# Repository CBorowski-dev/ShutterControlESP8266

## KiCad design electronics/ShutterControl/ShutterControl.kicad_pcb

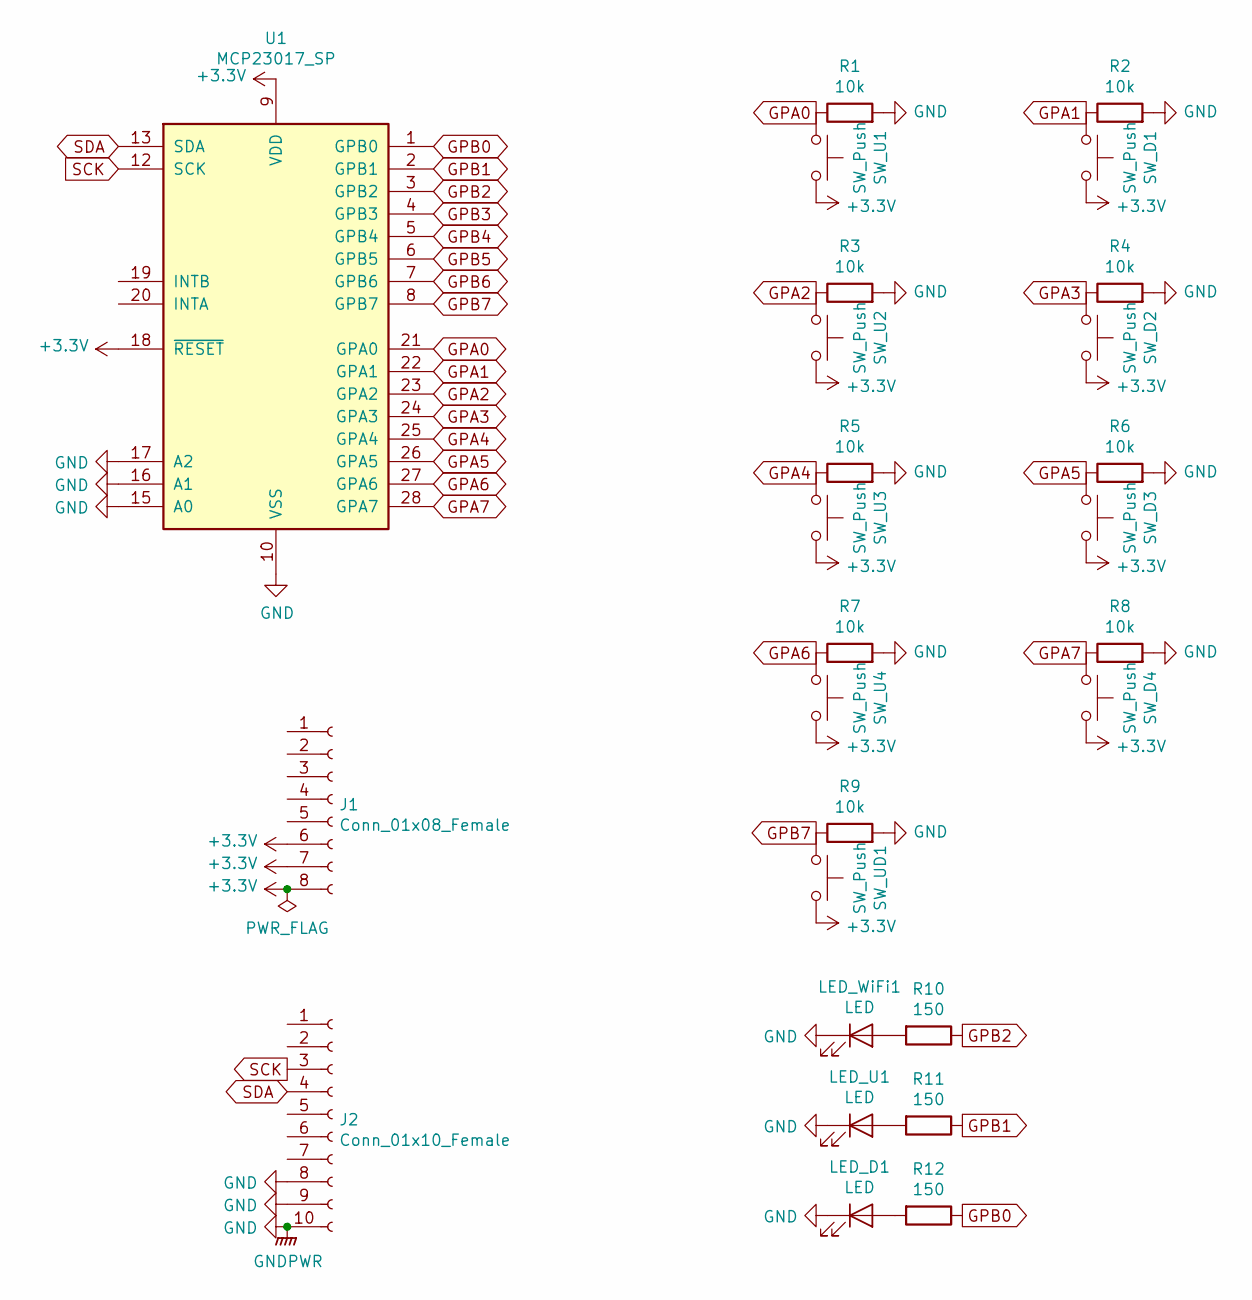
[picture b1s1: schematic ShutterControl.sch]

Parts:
J1: Conn_01x08_Female; PinHeader_1x08_P2.54mm_Vertical
J2: Conn_01x10_Female; PinHeader_1x10_P2.54mm_Vertical
LED_D1: LED; LED_D3.0mm_Clear
LED_U1: LED; LED_D3.0mm_Clear
LED_WiFi1: LED; LED_D3.0mm_Clear
R1, R2, R3, R4, R5, R6, R7, R8, R9: 10k; R_1206_3216Metric_Pad1.42x1.75mm_HandSolder
R10, R11, R12: 150; R_Axial_DIN0207_L6.3mm_D2.5mm_P2.54mm_Vertical
SW_D1, SW_D2, SW_D3, SW_D4: SW_Push; SW_PUSH_6mm_H7.3mm
SW_U1, SW_U2, SW_U3, SW_U4: SW_Push; SW_PUSH_6mm_H7.3mm
SW_UD1: SW_Push; SW_PUSH_6mm_H7.3mm
U1: MCP23017_SP; DIP-28_W7.62mm

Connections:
+3V3: J1.6, J1.7, J1.8, SW_D1.2, SW_D2.2, SW_D3.2, SW_D4.2, SW_U1.2, SW_U2.2, SW_U3.2, SW_U4.2, SW_UD1.2, U1.9 (VDD), U1.18 (~RESET~)
GND: J2.8, J2.9, J2.10, LED_D1.1 (K), LED_U1.1 (K), LED_WiFi1.1 (K), R1.2, R2.2, R3.2, R4.2, R5.2, R6.2, R7.2, R8.2, R9.2, U1.10 (VSS), U1.15 (A0), U1.16 (A1), U1.17 (A2)
GPA0: R1.1, SW_U1.1, U1.21 (GPA0)
GPA1: R2.1, SW_D1.1, U1.22 (GPA1)
GPA2: R3.1, SW_U2.1, U1.23 (GPA2)
GPA3: R4.1, SW_D2.1, U1.24 (GPA3)
GPA4: R5.1, SW_U3.1, U1.25 (GPA4)
GPA5: R6.1, SW_D3.1, U1.26 (GPA5)
GPA6: R7.1, SW_U4.1, U1.27 (GPA6)
GPA7: R8.1, SW_D4.1, U1.28 (GPA7)
GPB0: R12.1, U1.1 (GPB0)
GPB1: R11.1, U1.2 (GPB1)
GPB2: R10.1, U1.3 (GPB2)
GPB3: U1.4 (GPB3)
GPB4: U1.5 (GPB4)
GPB5: U1.6 (GPB5)
GPB6: U1.7 (GPB6)
GPB7: R9.1, SW_UD1.1, U1.8 (GPB7)
unnamed: LED_D1.2 (A), R12.2
unnamed: LED_U1.2 (A), R11.2
unnamed: LED_WiFi1.2 (A), R10.2
SCK: J2.3, U1.12 (SCK)
SDA: J2.4, U1.13 (SDA)

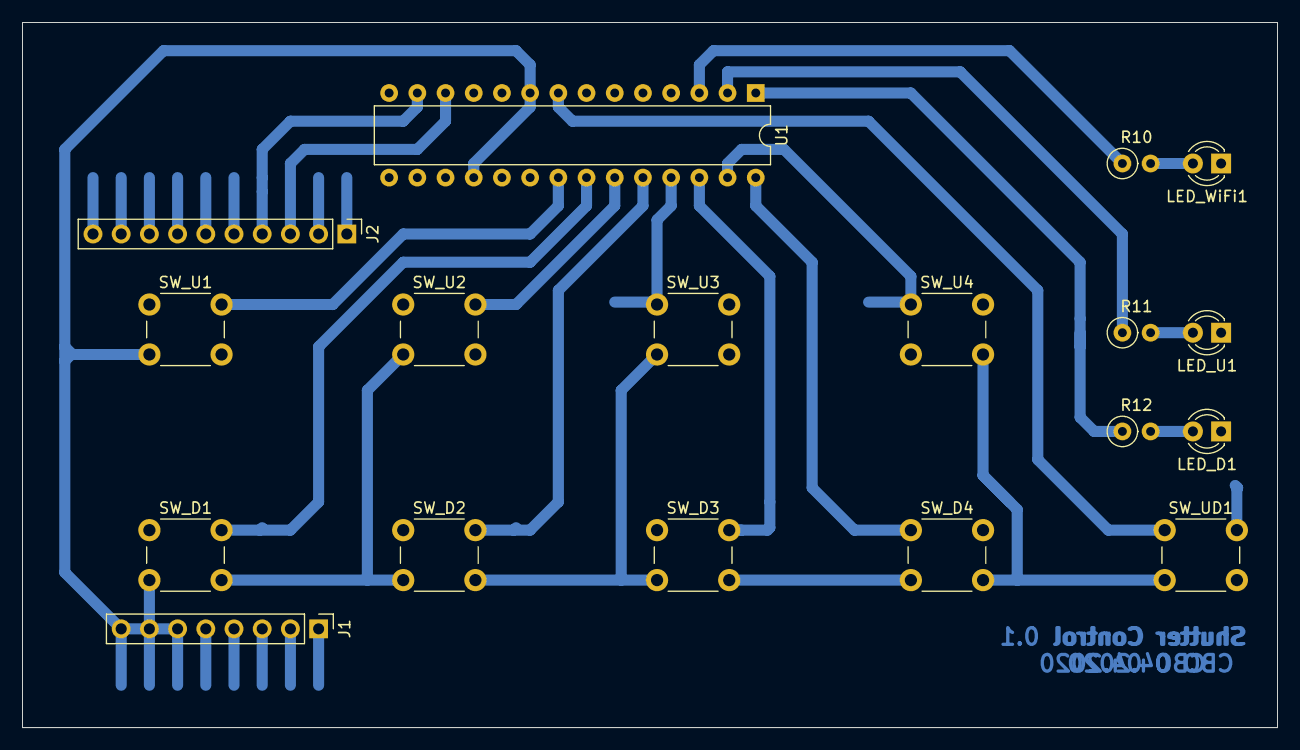
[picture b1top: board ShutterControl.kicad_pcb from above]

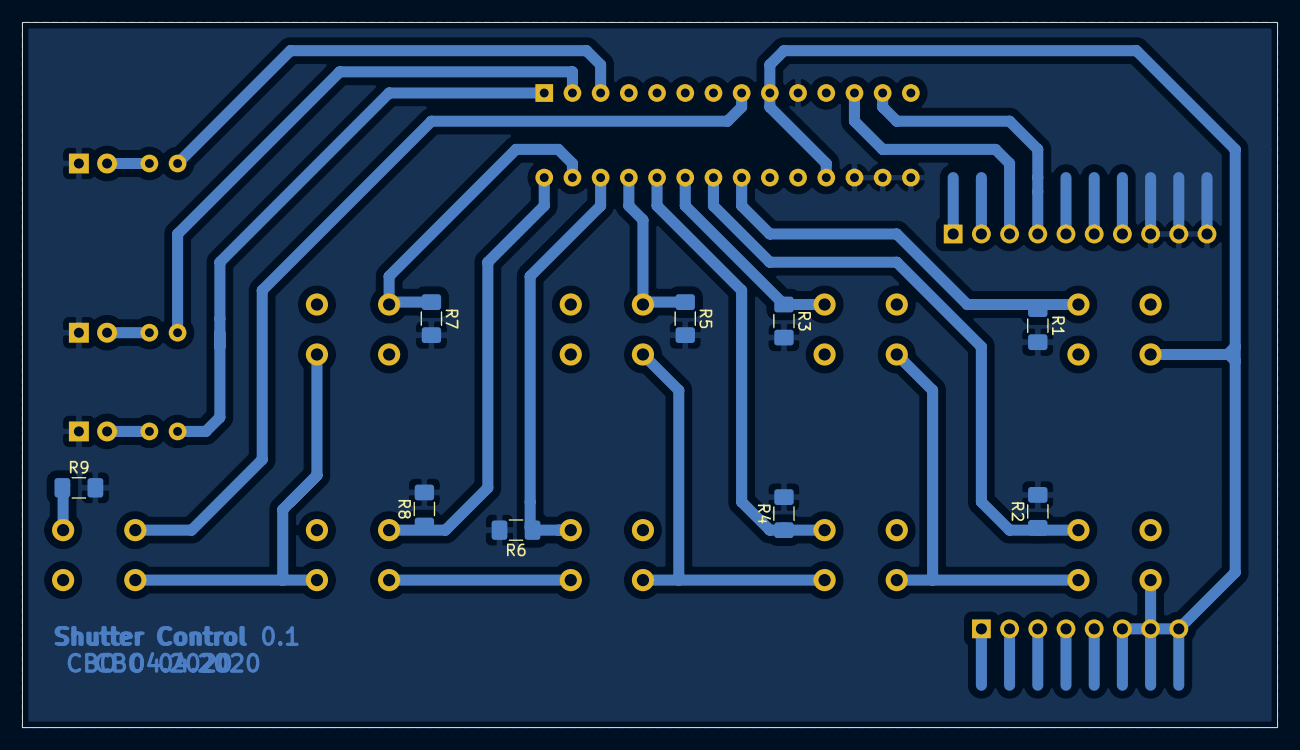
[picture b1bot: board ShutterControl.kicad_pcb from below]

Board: 2 copper layers, 113.0 x 63.5 mm, 27 parts (9 on the bottom side), 19 nets.

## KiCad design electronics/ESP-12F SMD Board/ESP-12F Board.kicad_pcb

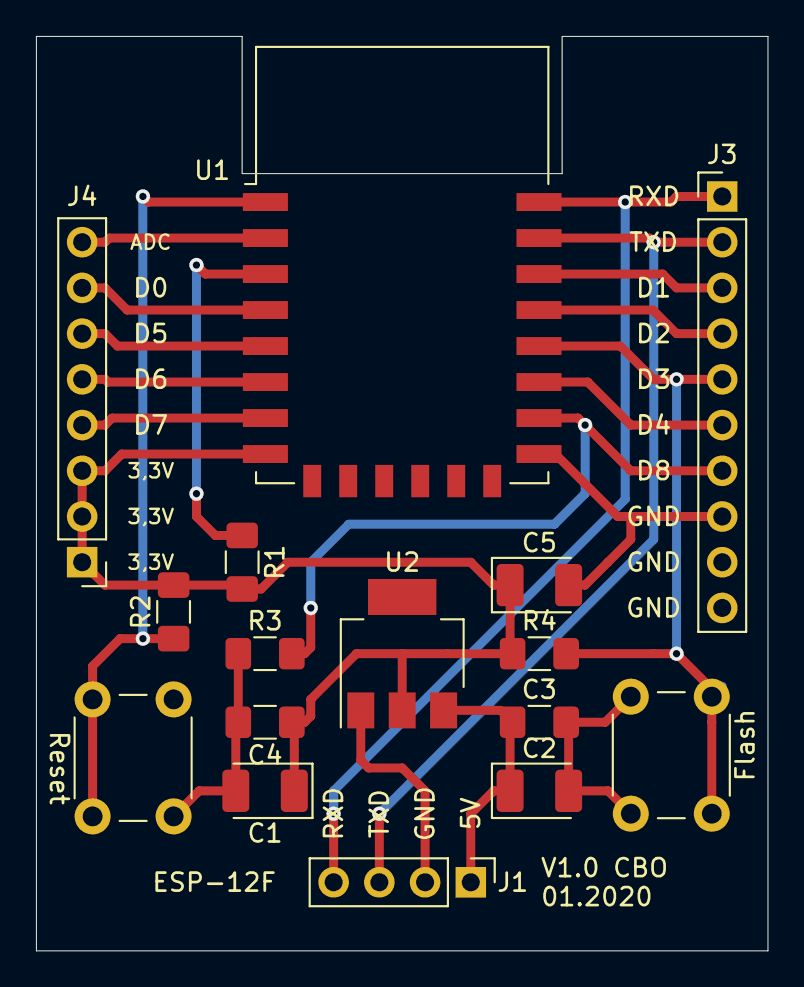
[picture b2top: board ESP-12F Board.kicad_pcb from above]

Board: 2 copper layers, 40.6 x 50.8 mm, 16 parts (0 on the bottom side), 17 nets.

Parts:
C1, C2: 22µF Tantal; CP_EIA-3528-21_Kemet-B_Pad1.50x2.35mm_HandSolder
C3, C4: 100nF Kerko; C_1206_3216Metric_Pad1.42x1.75mm_HandSolder
C5: 100µF Tantal; CP_EIA-3528-21_Kemet-B_Pad1.50x2.35mm_HandSolder
Flash: SW_Flash; SW_PUSH_6mm
J1: Conn_01x04_Male; PinHeader_1x04_P2.54mm_Vertical
J3: Conn_01x10_Male; PinHeader_1x10_P2.54mm_Vertical
J4: Conn_01x08_Male; PinHeader_1x08_P2.54mm_Vertical
R1, R2, R3, R4: 10k; R_1206_3216Metric_Pad1.42x1.75mm_HandSolder
Reset: SW_Reset; SW_PUSH_6mm
U1: ESP-12F; ESP-12E
U2: AMS1117-3.3; SOT-223

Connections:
+5V: C2.1, C3.1, J1.1, U2.3
/ADC: J4.8, U1.2
/GPIO0: Flash.2, J3.5, R4.2, U1.18
/GPIO2: J3.6, U1.17
/GPIO4: J3.4, U1.19
/GPIO5: J3.3, U1.20
/GPIO12: J4.5, U1.6
/GPIO13: J4.4, U1.7
/GPIO14: J4.6, U1.5
/GPIO15: J3.7, R3.2, U1.16
/GPIO16: J4.7, U1.4
/RXD: J1.4, J3.1, U1.22
/TXD: J1.3, J3.2, U1.21
/VCC: C1.1, C4.1, C5.1, J4.1, J4.2, J4.3, R1.2, R2.2, R4.1, U1.8, U2.2
GND: C1.2, C2.2, C3.2, C4.2, C5.2, Flash.1, J1.2, J3.8, J3.9, J3.10, R3.1, Reset.1, U1.15, U2.1
unnamed: R1.1, U1.3
unnamed: R2.1, Reset.2, U1.1

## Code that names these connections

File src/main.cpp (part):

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//
// 1. Change the configuration to 'Sonoff Dual R2 (39)'
// 2. Configure GPIO1 & GPIO9:
//    GPIO0 --> Switch1 (9)
//    GPIO9 --> Switch2 (10)
// 3. Set 'Interlock on' per Tasmota console
// 4. Deactivate old rules:
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  mcp.begin_I2C();      // use default address 0

  // How MCP23017 pins are addressed
  // Pin 0 <-> GPA0
  // ...
  // Pin 7 <-> GPA7
  // Pin 8 <-> GPB0
  // ...
  // Pin 15 <-> GPb7

  // LEDs
  mcp.pinMode(DOWN_LED_PIN, OUTPUT); // Downstairs LED
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  mcp.pinMode(WIFI_LED_PIN, OUTPUT); // WiFi information LED

  // Buttons
  mcp.pinMode(0, INPUT); // 1'st shutter up <-> GPA0
  mcp.pinMode(1, INPUT); // 1'st shutter down <-> GPA1
  mcp.pinMode(2, INPUT); // 2'nd shutter up <-> GPA2
  mcp.pinMode(3, INPUT); // 2'nd shutter down <-> GPA3
  mcp.pinMode(4, INPUT); // 3'rd shutter up <-> GPA4
  mcp.pinMode(5, INPUT); // 3'rd shutter down <-> GPA5
  mcp.pinMode(6, INPUT); // 4'th shutter up <-> GPA6
  mcp.pinMode(7, INPUT); // 4'th shutter down <-> GPA7
  mcp.pinMode(15, INPUT); // upstairs/downstairs button <-> GPB7
}

void reconnect() {
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      }
      mqttClient.loop();

      // Port A pins GPA0, GPA2, GPA4, GPA6 are for devices (shutters 1-4 direction up / lights 1-4 on)
      // shutters/lights 1-4 are mapped to the first 4 bits: 1->bit 0; 2->bit 2; 3->bit 4; 4->bit 6
      selectedDevices = 0;
      for (uint8_t i = 0; i<7; i+=2) {
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        }
      }

      // Port A pins GPA1, GPA3, GPA5, GPA7 are for devices (shutters 1-4 direction down / lights 1-4 off)
      // shutters/lights 1-4 are mapped to the first 4 bits: 1->bit 1; 2->bit 3; 3->bit 5; 4->bit 7
      selectedDevices = 0;
      for (uint8_t i = 1; i<8; i+=2) {
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
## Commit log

2020-05-11 Initial version
2020-10-04 Changes due to add hardware buttons
2022-11-26 Update to support also lights
2025-10-25 Added additional lights
